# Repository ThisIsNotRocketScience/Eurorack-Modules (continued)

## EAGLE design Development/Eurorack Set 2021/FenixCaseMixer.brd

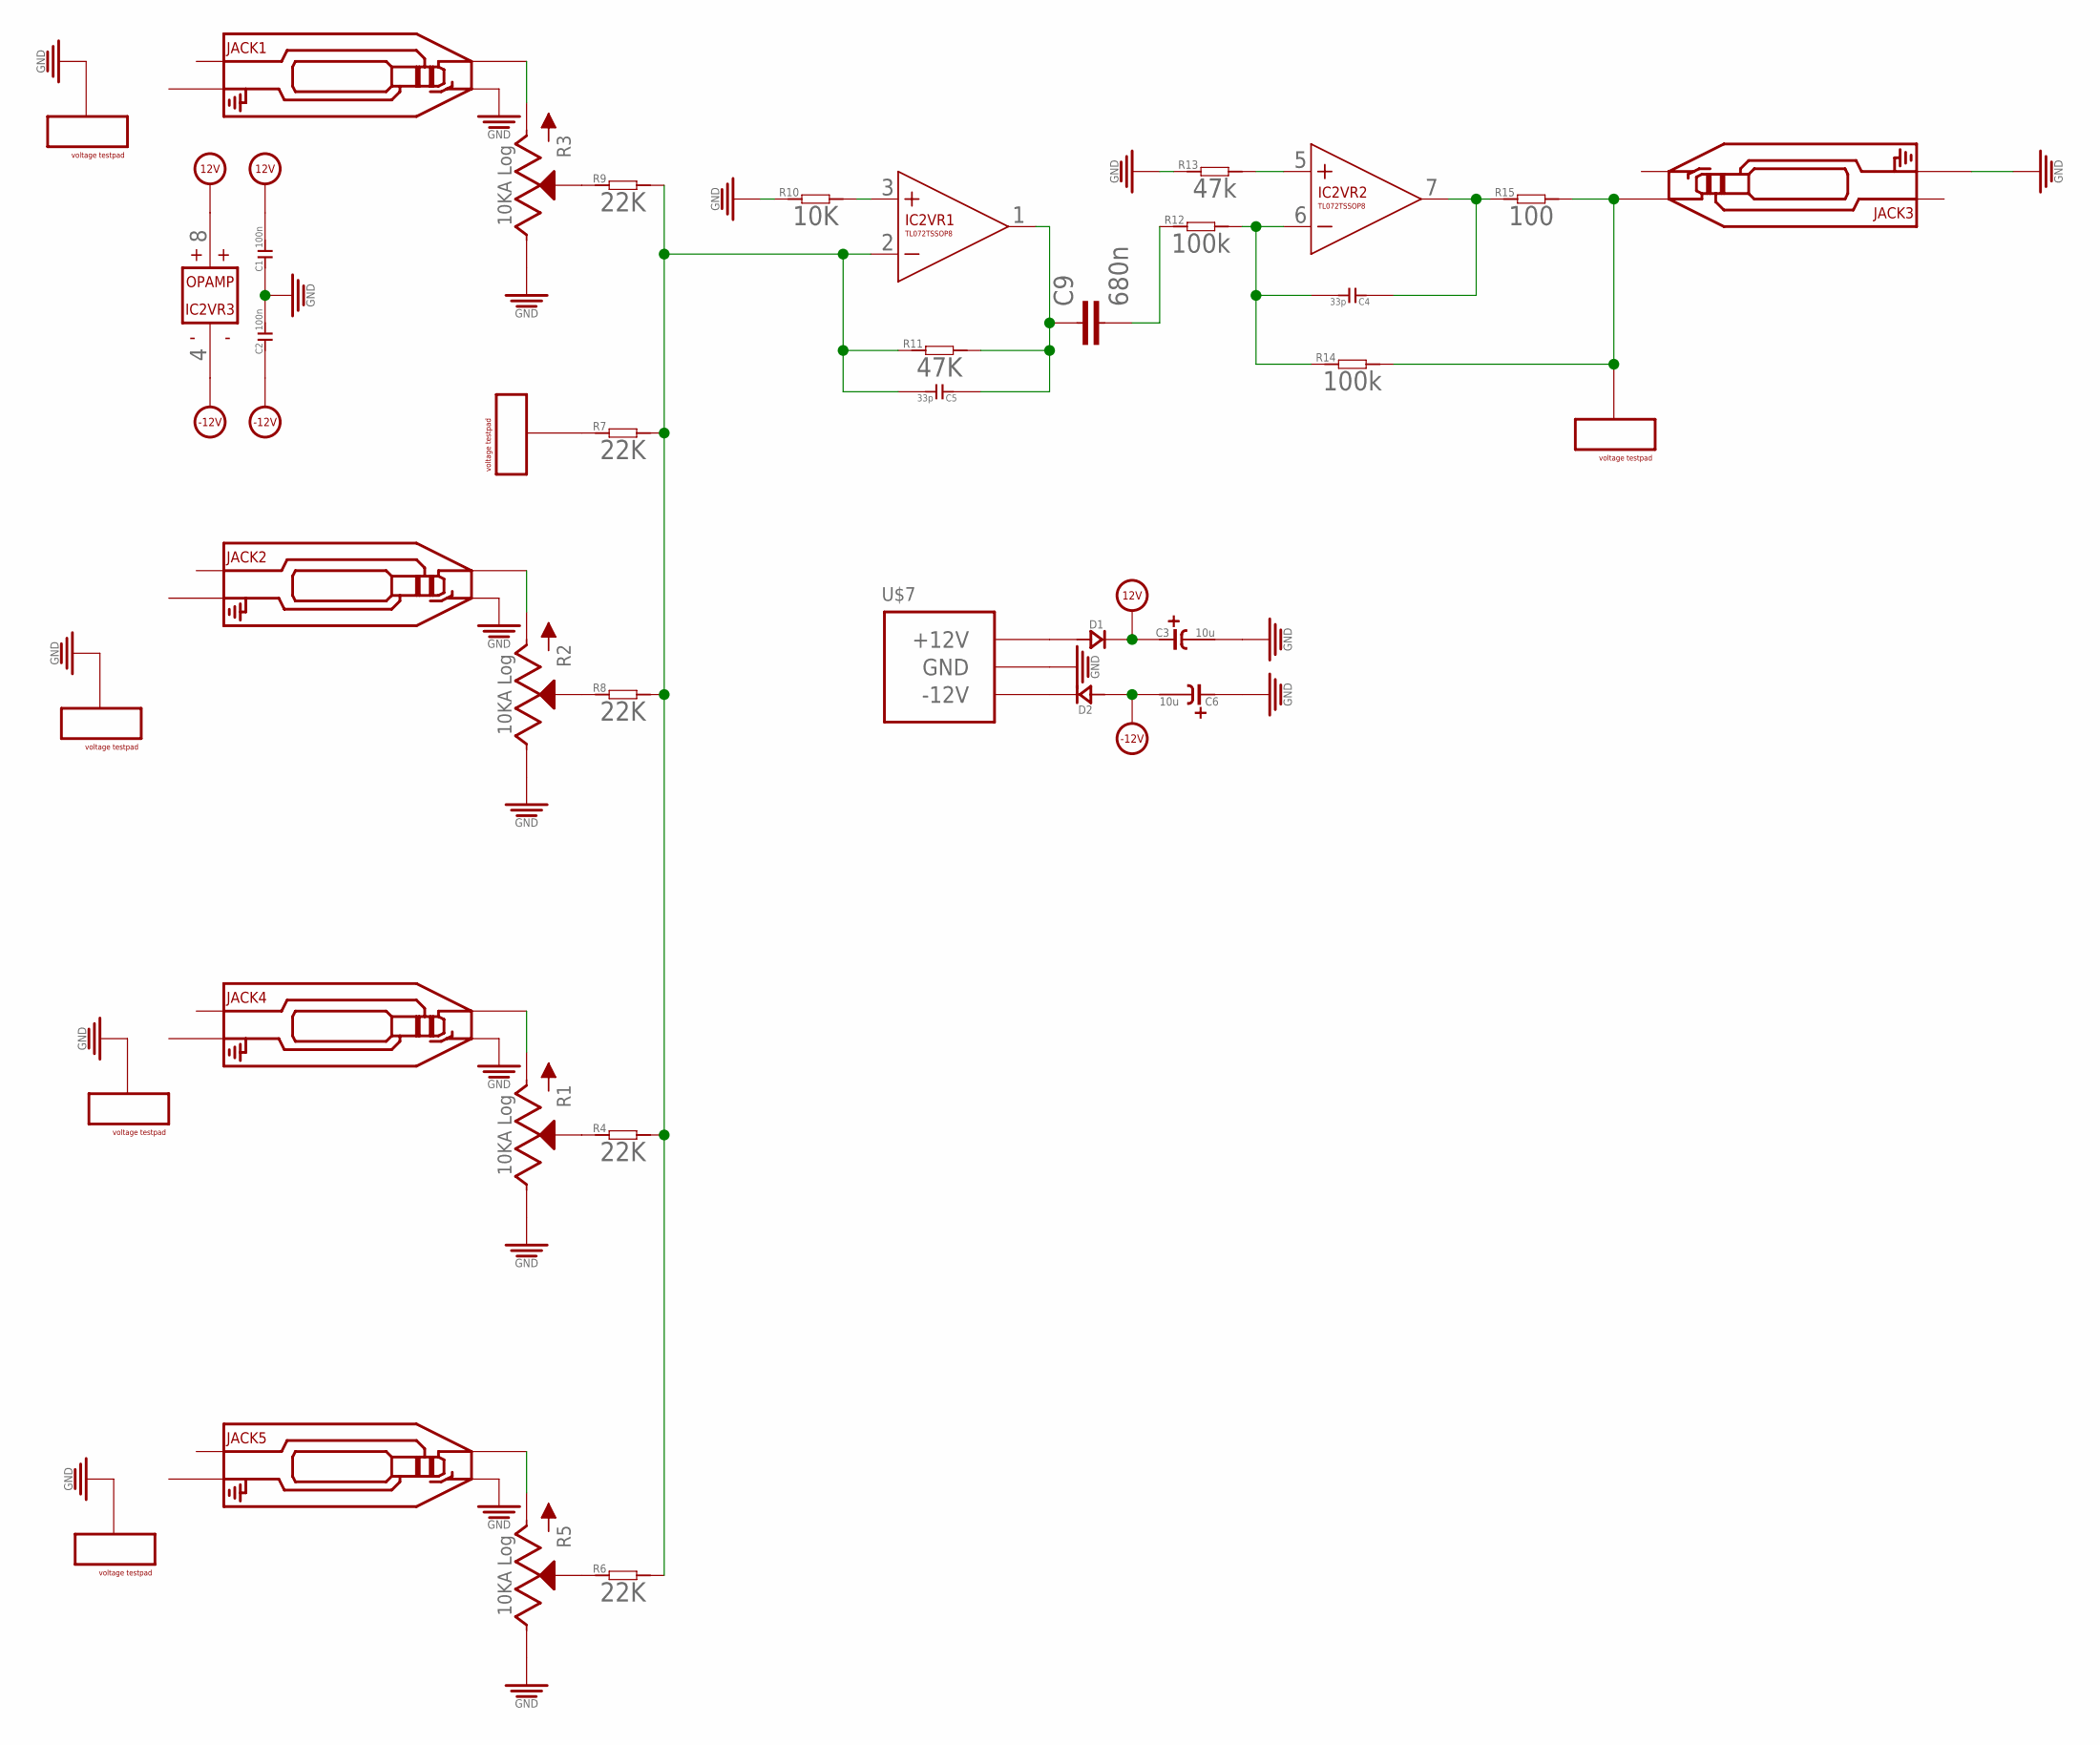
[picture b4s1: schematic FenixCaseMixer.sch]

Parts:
C1, C2: 100n; C0603
C3, C6: 10u; CASE-A_3216
C4, C5: 33p; C0603
C9: 680n; C5B4.5
D1, D2: D-SMA; DO-214AC
IC2: TL072TSSOP8; TSSOP8
JACK1, JACK2, JACK3, JACK4, JACK5: AUDIO-JACK_SMALLSYMBOL; 3.5MM-JACK-SWITCH-13MM-NOHOLES-TESTPAD
R1, R2, R3, R5: 10KA Log; ALPS_POT_SQUAREHOLES
R4, R6, R7, R8, R9: 22K; R0603
R10: 10K; R0603
R11: 47K; R0603
R12, R14: 100k; R0603
R13: 47k; R0603
R15: 100; R0603
U$5, U$6: VOLTAGETESTPAD_BIG; POWERTESTPAD_BIG
U$7: POWER_SIMPLE10; POWER_10
U$10, U$11, U$12, U$13: VOLTAGETESTPAD; POWERTESTPAD

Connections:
12V: C1.2, C3.+ (1), D1.2 (-), IC2.8 (V+)
-12V: C2.1, C6.- (2), D2.1 (+), IC2.4 (V-)
GND: C1.1, C2.2, C3.- (2), C6.+ (1), JACK1.SWITCH_B@1 (SWITCH), JACK1.SWITCH_T@3 (SWITCH), JACK2.SWITCH_B@1 (SWITCH), JACK2.SWITCH_T@3 (SWITCH), JACK3.RING_B@1 (RING), JACK3.RING_T@3 (RING), JACK4.SWITCH_B@1 (SWITCH), JACK4.SWITCH_T@3 (SWITCH), JACK5.SWITCH_B@1 (SWITCH), JACK5.SWITCH_T@3 (SWITCH), R1.P$1 (E), R2.P$1 (E), R3.P$1 (E), R5.P$1 (E), R10.1, R13.1, U$7.3 (GND), U$7.4 (GND), U$7.5 (GND), U$7.6 (GND), U$7.7 (GND), U$7.8 (GND), U$10.P$1, U$10.P$2, U$10.P$3, U$11.P$1, U$11.P$2, U$11.P$3, U$12.P$1, U$12.P$2, U$12.P$3, U$13.P$1, U$13.P$2, U$13.P$3
MIXO: JACK3.TIP_B@1 (TIP), JACK3.TIP_T@3 (TIP), R14.2, R15.2, U$6.P$1, U$6.P$2, U$6.P$3
unnamed: JACK1.TIP_B@1 (TIP), JACK1.TIP_T@3 (TIP), R3.P$3 (A)
unnamed: JACK2.TIP_B@1 (TIP), JACK2.TIP_T@3 (TIP), R2.P$3 (A)
unnamed: JACK4.TIP_B@1 (TIP), JACK4.TIP_T@3 (TIP), R1.P$3 (A)
unnamed: R1.P$2 (S), R4.1
unnamed: R7.1, U$5.P$1, U$5.P$2, U$5.P$3
unnamed: JACK5.TIP_B@1 (TIP), JACK5.TIP_T@3 (TIP), R5.P$3 (A)
unnamed: R2.P$2 (S), R8.1
unnamed: C5.2, IC2.2 (-IN), R4.2, R6.2, R7.2, R8.2, R9.2, R11.1
unnamed: R3.P$2 (S), R9.1
unnamed: IC2.3 (+IN), R10.2
unnamed: C5.1, C9.1, IC2.1 (OUT), R11.2
unnamed: IC2.5 (+IN), R13.2
unnamed: C4.2, IC2.6 (-IN), R12.2, R14.1
unnamed: C4.1, IC2.7 (OUT), R15.1
unnamed: C9.2, R12.1
unnamed: R5.P$2 (S), R6.1
unnamed: D1.1 (+), U$7.9 (+12V), U$7.10 (+12V)
unnamed: D2.2 (-), U$7.1 (-12V), U$7.2 (-12V)

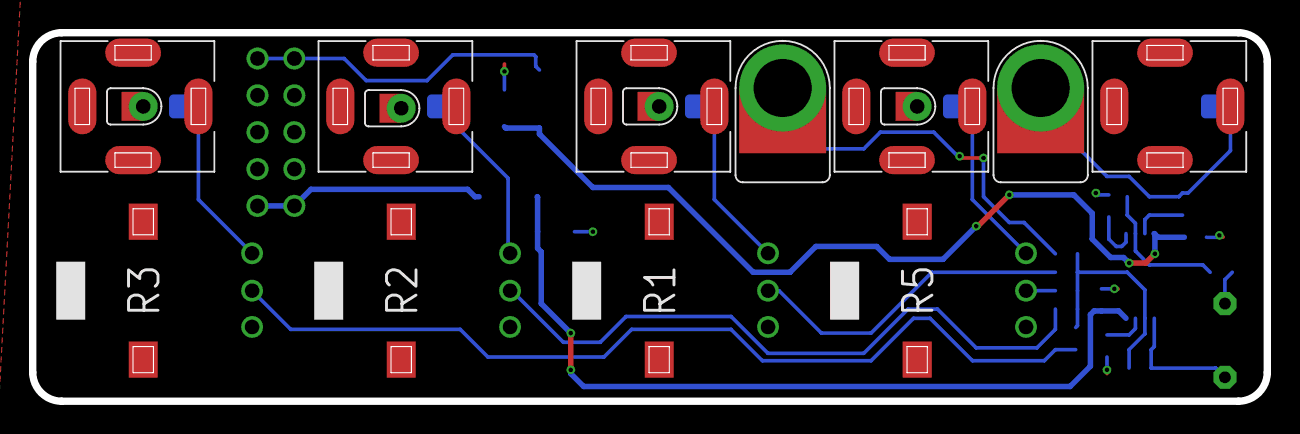
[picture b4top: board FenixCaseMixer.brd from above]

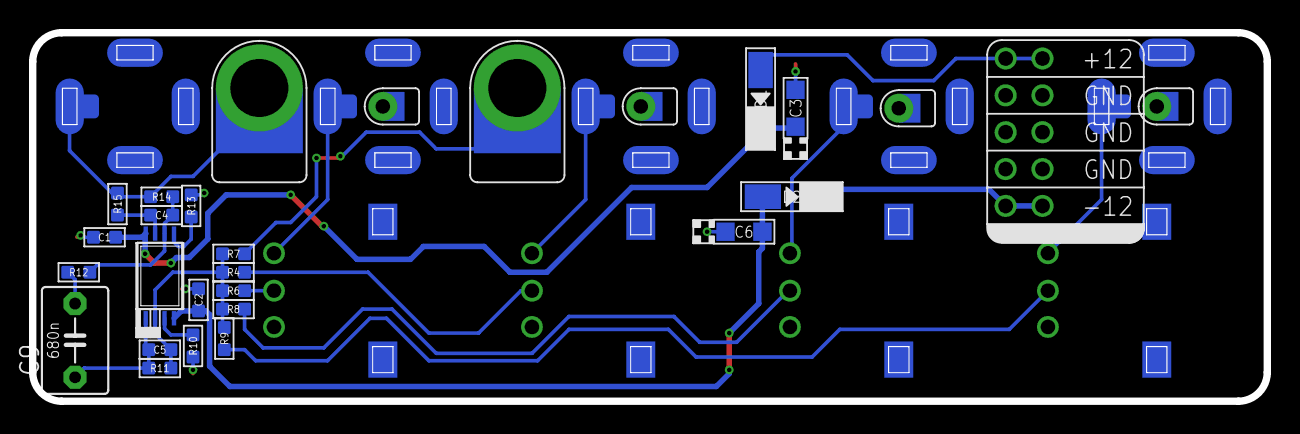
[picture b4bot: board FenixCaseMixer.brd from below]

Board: 2 copper layers, 85.1 x 25.4 mm, 37 parts (22 on the bottom side), 22 nets.

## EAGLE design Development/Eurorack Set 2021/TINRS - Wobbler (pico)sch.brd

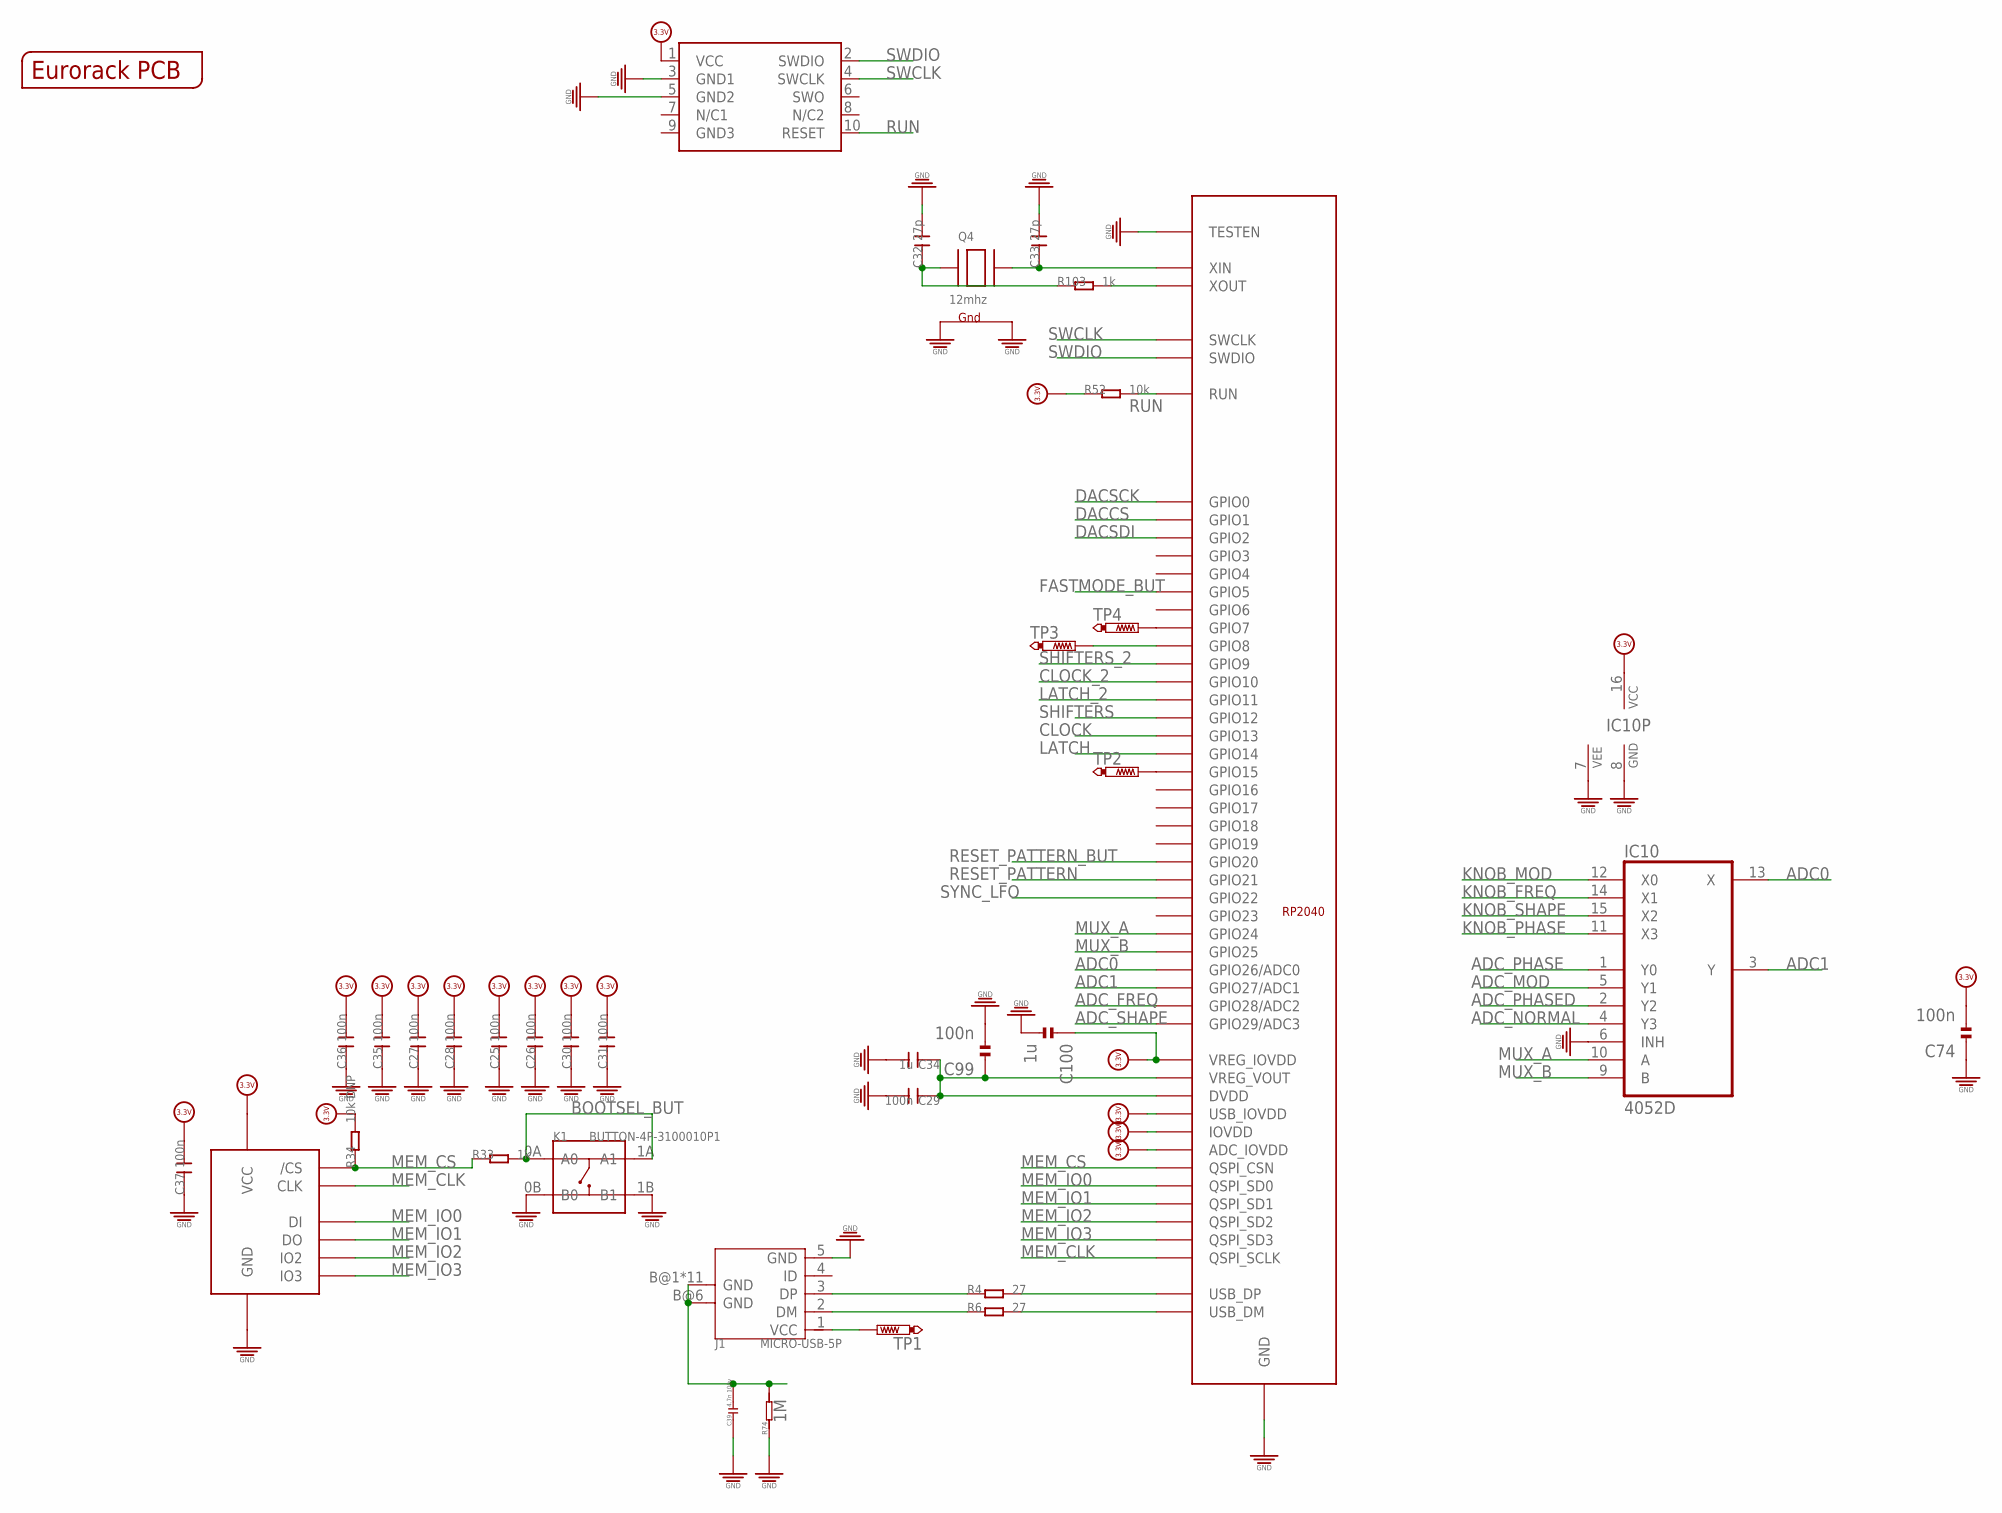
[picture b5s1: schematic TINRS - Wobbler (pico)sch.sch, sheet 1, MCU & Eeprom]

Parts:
C25, C26, C27, C28, C29, C30, C31, C35, C36, C37, C74, C99: 100n; C0402
C32, C33: 27p; C0402
C34, C100: 1u; C0402
C39: 4.7n 100v; C3216
IC10: 4052D; SO16
J1: MICRO-USB-5P; C132563
K1: BUTTON-4P-3100010P1; 4P-SMD-6.0X6.0X5.0H
OUTLINE: EURORACK_PCB12HP; EURORACK12HPPCB
Q4: 12mhz; NX3225
R4, R6: 27; R0402
R33, R103: 1k; R0402
R34: 10k DNP; R0402
R52: 10k; R0402
R74: 1M; R0603
SWD2: CORTEX_SWD; M50-3600542
TP1, TP2, TP3, TP4: PTR1B1,27; B1,27
U$2: RP2040; QFN-56
U$25: W25Q256JVEIQTR; SOIC-8

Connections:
1.1V: C29.1, C34.1, C99.1, U$2.P$23 (DVDD), U$2.P$45 (VREG_VOUT), U$2.P$50 (DVDD)
3.3V: C25.2, C26.2, C27.2, C28.2, C30.2, C31.2, C35.2, C36.2, C37.2, C74.2, C100.1, IC10.16 (VCC), R34.2, R52.1, SWD2.1 (VCC), U$2.P$1 (IOVDD), U$2.P$10 (IOVDD), U$2.P$22 (IOVDD), U$2.P$33 (IOVDD), U$2.P$42 (IOVDD), U$2.P$43 (ADC_IOVDD), U$2.P$44 (VREG_IOVDD), U$2.P$48 (USB_IOVDD), U$2.P$49 (IOVDD), U$25.8 (VCC); also elsewhere on the board
ADC0: IC10.13 (X), U$2.P$38 (GPIO26/ADC0)
ADC1: IC10.3 (Y), U$2.P$39 (GPIO27/ADC1)
ADC_FREQ: U$2.P$40 (GPIO28/ADC2); also elsewhere on the board
ADC_MOD: IC10.5 (Y1); also elsewhere on the board
ADC_NORMAL: IC10.4 (Y3); also elsewhere on the board
ADC_PHASE: IC10.1 (Y0); also elsewhere on the board
ADC_PHASED: IC10.2 (Y2); also elsewhere on the board
ADC_SHAPE: U$2.P$41 (GPIO29/ADC3); also elsewhere on the board
BOOTSEL_BUT: K1.0A (A0), K1.1A (A1), R33.2
CLOCK: U$2.P$16 (GPIO13); also elsewhere on the board
CLOCK_2: U$2.P$13 (GPIO10); also elsewhere on the board
DACCS: U$2.P$3 (GPIO1); also elsewhere on the board
DACSCK: U$2.P$2 (GPIO0); also elsewhere on the board
DACSDI: U$2.P$4 (GPIO2); also elsewhere on the board
FASTMODE_BUT: U$2.P$7 (GPIO5); also elsewhere on the board
GND: C25.1, C26.1, C27.1, C28.1, C29.2, C30.1, C31.1, C32.2, C33.2, C34.2, C35.1, C36.1, C37.1, C39.P$1 (1), C74.1, C99.2, C100.2, IC10.6 (INH), IC10.7 (VEE), IC10.8 (GND), J1.5 (GND), K1.0B (B0), K1.1B (B1), Q4.2 (G2), Q4.4 (G1), R74.1, SWD2.3 (GND1), SWD2.5 (GND2), U$2.GND, U$2.P$19 (TESTEN), U$25.4 (GND); also elsewhere on the board
KNOB_FREQ: IC10.14 (X1); also elsewhere on the board
KNOB_MOD: IC10.12 (X0); also elsewhere on the board
KNOB_PHASE: IC10.11 (X3); also elsewhere on the board
KNOB_SHAPE: IC10.15 (X2); also elsewhere on the board
LATCH: U$2.P$17 (GPIO14); also elsewhere on the board
LATCH_2: U$2.P$14 (GPIO11); also elsewhere on the board
MEM_CLK: U$2.P$52 (QSPI_SCLK), U$25.6 (CLK)
MEM_CS: R33.1, R34.1, U$2.P$56 (QSPI_CSN), U$25.1 (/CS)
MEM_IO0: U$2.P$53 (QSPI_SD0), U$25.5 (DI)
MEM_IO1: U$2.P$55 (QSPI_SD1), U$25.2 (DO)
MEM_IO2: U$2.P$54 (QSPI_SD2), U$25.3 (IO2)
MEM_IO3: U$2.P$51 (QSPI_SD3), U$25.7 (IO3)
MUX_A: IC10.10 (A), U$2.P$36 (GPIO24)
MUX_B: IC10.9 (B), U$2.P$37 (GPIO25)
unnamed: C33.1, Q4.3 (X2), U$2.P$20 (XIN)
unnamed: C32.1, Q4.1 (X1), R103.1
unnamed: R4.2, U$2.P$47 (USB_DP)
unnamed: R6.2, U$2.P$46 (USB_DM)
unnamed: C39.P$2 (2), J1.B@1 (GND), J1.B@2 (GND), J1.B@3 (GND), J1.B@4 (GND), J1.B@5 (GND), J1.B@6 (GND), J1.B@7 (GND), J1.B@8 (GND), J1.B@9 (GND), J1.B@10 (GND), J1.B@11 (GND), J1.B@12 (GND), R74.2
unnamed: J1.1 (VCC), TP1.TP
unnamed: TP2.TP, U$2.P$18 (GPIO15)
unnamed: TP4.TP, U$2.P$9 (GPIO7)
unnamed: R103.2, U$2.P$21 (XOUT)
unnamed: TP3.TP, U$2.P$11 (GPIO8)
RESET_PATTERN: U$2.P$32 (GPIO21); also elsewhere on the board
RESET_PATTERN_BUT: U$2.P$31 (GPIO20); also elsewhere on the board
RUN: R52.2, SWD2.10 (RESET), U$2.P$26 (RUN)
SHIFTERS: U$2.P$15 (GPIO12); also elsewhere on the board
SHIFTERS_2: U$2.P$12 (GPIO9); also elsewhere on the board
SWCLK: SWD2.4 (SWCLK), U$2.P$24 (SWCLK)
SWDIO: SWD2.2 (SWDIO), U$2.P$25 (SWDIO)
SYNC_LFO: U$2.P$34 (GPIO22); also elsewhere on the board
USB_N: J1.2 (DM), R6.1
USB_P: J1.3 (DP), R4.1
